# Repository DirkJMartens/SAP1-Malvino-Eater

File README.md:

# SAP1-Malvino-Eater
Wire wrapped implementation of Albert Malvino's SAP1 computer, similar to Ben Eater's "8 bit CPU". 

Like thousands of others, I watched Ben Eater's YouTube series on how to "Build an 8-bit CPU from scratch". 
Ben's video series is based on the "SAP-1 (Simple As Possible 1)" computer, described in "Digital Computer Electronics" 
book by Albert Malvino and Jerald Brown, first released in 1977. 

And like thousands of others, I wanted to build my own. Partly to learn a few things, but above all for fun. 
But I also wanted a few differences: 
  - Use wire-wrapping instead of breadboards. As I could only work on it mostly on weekends and in my spare time,
    I wanted it to be longer-lasting so I could put it away easily and pull it out without first spending time to
    find which wires have been dislodged to get it back working again. 
  - Stay closer to Malvino's original design for the SAP-1. 
  - Add some blinkenlights to visualize:
    - LED bar graphs for W-bus, Accu, B-register, Output-register, Instruction register 
    - LEDs for the control signals (La, Ea, Lb, Eb, Ep, CE ...) and the Program Counter 
    - the ring counter indicating the stage of the Fetch/Execute cycle 
    - the instruction decoder 
  - Added a dual 7-segment display to visualize the W-bus content in HEX-format instead of in binary via LED bar graph.

In short, I wanted it to be much more of a visual CPU that can show which signal gets activated and what it triggers 
in various parts of the CPU. Because I wanted the wiring to be visible, I did not use wire-wrap sockets and wire on the 
bottom of the perfboard. Instead, I soldered pin headers next to each row of IC pins so I had access to each pin on the 
top and wire-wrapped from pinheader pin to pinheader pin. 

Most important specs: 
  - 4 bits address bus with 16 bytes RAM memory and an 8 bits data bus 
  - 4 instructions: Load, Add, Sub and Out
  - Opcodes is the most-significant-nibble (top 4 bits) and memory location is the least (bottom 4 bits) 
  - Clock signal can be single stepped, or auto-run with variable clock speed (up to a few dozen Hz)
  - Done using a mix of various 74-series ICs (LS, F ...) and implemented on a 20cmx30cm (8"x12") perfboard.

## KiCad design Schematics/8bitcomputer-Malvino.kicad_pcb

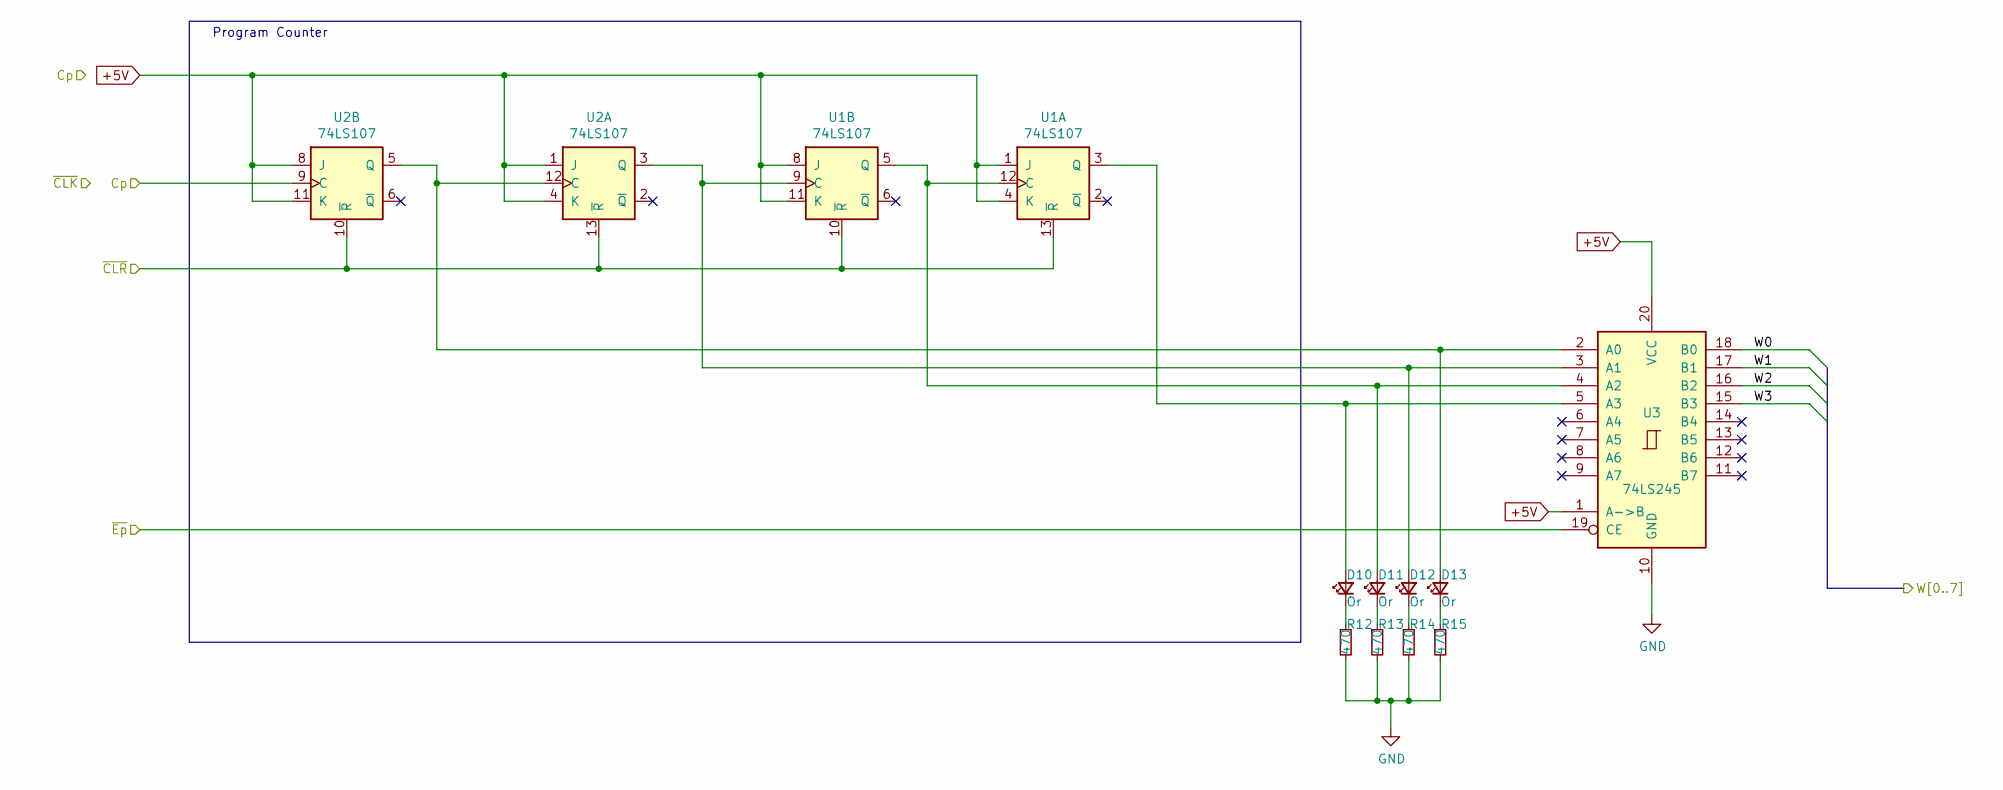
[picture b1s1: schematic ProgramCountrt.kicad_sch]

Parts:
D10, D11, D12, D13: Or; LED_D3.0mm
R12, R13, R14, R15: 470; R_0805_2012Metric
U1, U2: 74LS107; DIP-14_W7.62mm_LongPads
U3: 74LS245; DIP-20_W7.62mm_LongPads

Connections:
+5V: U1.1 (J), U1.4 (K), U1.8 (J), U1.11 (K), U2.1 (J), U2.4 (K), U2.8 (J), U2.11 (K), U3.1 (A->B), U3.20 (VCC); also elsewhere on the board
/1-PowerClock/~CLR: U1.10 (~R), U1.13 (~R), U2.10 (~R), U2.13 (~R); also elsewhere on the board
/2-ProgramCounter/~Ep: U3.19 (CE); also elsewhere on the board
/4-16x8RAM/W0: U3.18 (B0); also elsewhere on the board
/4-16x8RAM/W1: U3.17 (B1); also elsewhere on the board
/4-16x8RAM/W2: U3.16 (B2); also elsewhere on the board
/4-16x8RAM/W3: U3.15 (B3); also elsewhere on the board
/9-InstrControlRing/T2: U2.9 (C); also elsewhere on the board
GND: R12.2, R13.2, R14.2, R15.2, U3.10 (GND); also elsewhere on the board
unnamed: D10.1 (K), R12.1
unnamed: D10.2 (A), U1.3 (Q), U3.5 (A3)
unnamed: D11.1 (K), R13.1
unnamed: D11.2 (A), U1.5 (Q), U1.12 (C), U3.4 (A2)
unnamed: D12.1 (K), R14.1
unnamed: D12.2 (A), U1.9 (C), U2.3 (Q), U3.3 (A1)
unnamed: D13.1 (K), R15.1
unnamed: D13.2 (A), U2.5 (Q), U2.12 (C), U3.2 (A0)

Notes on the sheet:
Program Counter

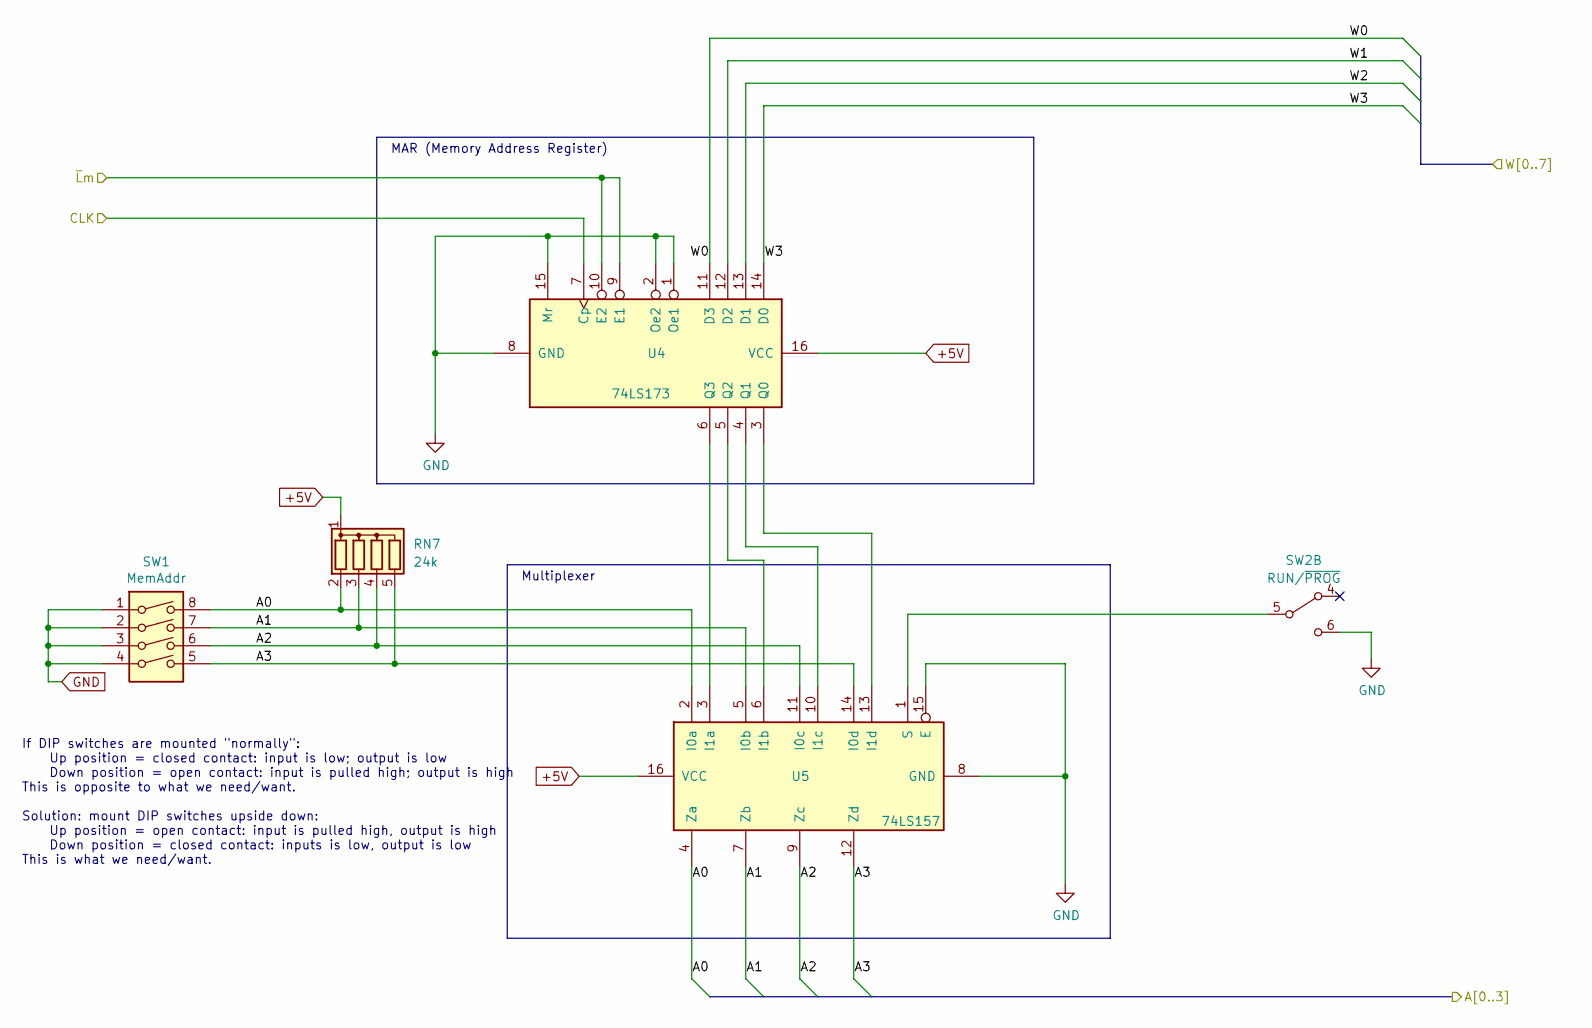
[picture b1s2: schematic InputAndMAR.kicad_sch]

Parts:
RN7: 24k; R_Array_SIP5
SW1: MemAddr; SW_DIP_SPSTx04_Slide_9.78x12.34mm_W7.62mm_P2.54mm
SW2: RUN/~{PROG}; SW_CuK_JS202011AQN_DPDT_Angled
U4: 74LS173; DIP-16_W7.62mm_LongPads
U5: 74LS157; DIP-16_W7.62mm_LongPads

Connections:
+5V: RN7.1 (common), U4.16 (VCC), U5.16 (VCC); also elsewhere on the board
/1-PowerClock/CLK: U4.7 (Cp); also elsewhere on the board
/3-InputAndMAR/A0: RN7.2 (R1), SW1.8, U5.2 (I0a), U5.4 (Za); also elsewhere on the board
/3-InputAndMAR/A1: RN7.3 (R2), SW1.7, U5.5 (I0b), U5.7 (Zb); also elsewhere on the board
/3-InputAndMAR/A2: RN7.4 (R3), SW1.6, U5.9 (Zc), U5.11 (I0c); also elsewhere on the board
/3-InputAndMAR/A3: RN7.5 (R4), SW1.5, U5.12 (Zd), U5.14 (I0d); also elsewhere on the board
/3-InputAndMAR/~Lm: U4.9 (E1), U4.10 (E2); also elsewhere on the board
/4-16x8RAM/W0: U4.11 (D3); also elsewhere on the board
/4-16x8RAM/W1: U4.12 (D2); also elsewhere on the board
/4-16x8RAM/W2: U4.13 (D1); also elsewhere on the board
/4-16x8RAM/W3: U4.14 (D0); also elsewhere on the board
GND: SW1.1, SW1.2, SW1.3, SW1.4, SW2.6 (C), U4.1 (Oe1), U4.2 (Oe2), U4.8 (GND), U4.15 (Mr), U5.8 (GND), U5.15 (E); also elsewhere on the board
unnamed: U4.3 (Q0), U5.13 (I1d)
unnamed: U4.4 (Q1), U5.10 (I1c)
unnamed: U4.5 (Q2), U5.6 (I1b)
unnamed: U4.6 (Q3), U5.3 (I1a)
unnamed: SW2.5 (B), U5.1 (S)

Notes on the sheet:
Multiplexer
If DIP switches are mounted "normally": Up position = closed contact: input is low; output is low Down position = open contact: input is pulled high; output is high This is opposite to what we need/want. Solution: mount DIP switches upside down: Up position = open contact: input is pulled high, out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
MAR (Memory Address Register)

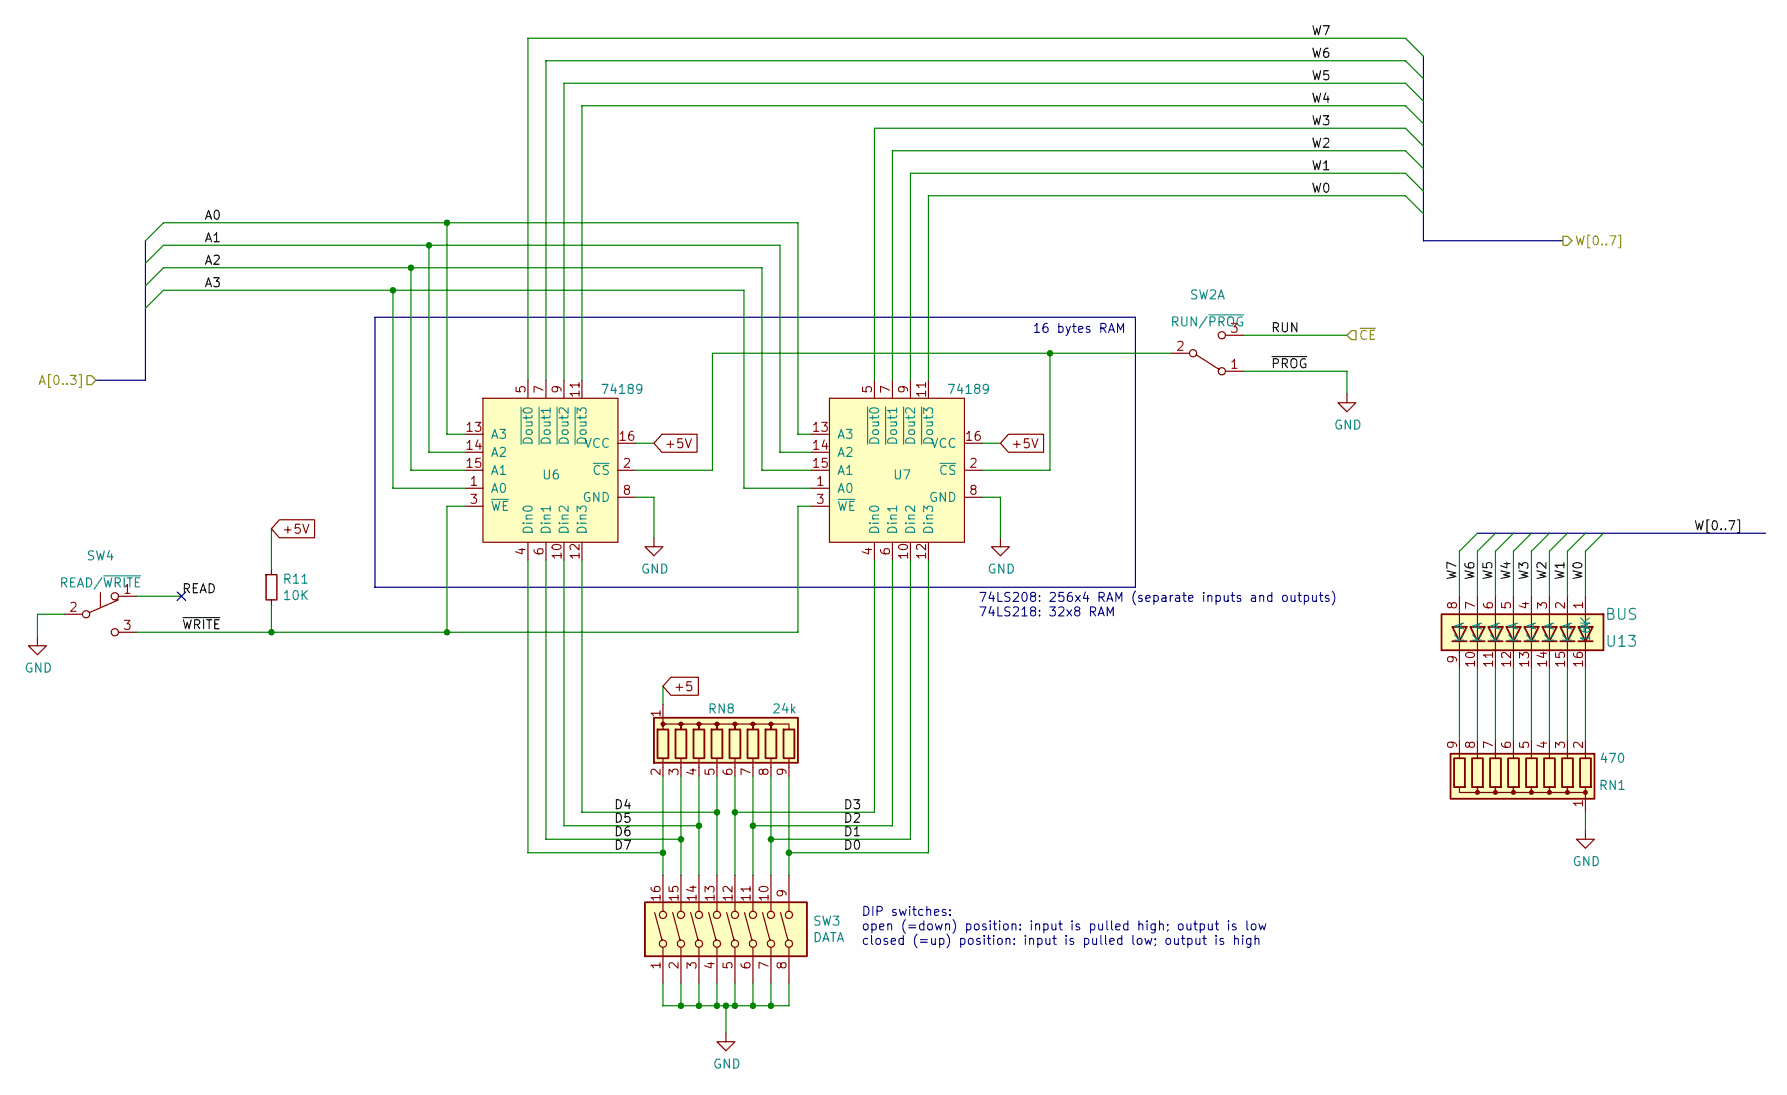
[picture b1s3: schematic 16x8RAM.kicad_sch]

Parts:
R11: 10K; R_Axial_DIN0207_L6.3mm_D2.5mm_P7.62mm_Horizontal
RN1: 470; R_Array_SIP9
RN8: 24k; R_Array_SIP9
SW2: RUN/~{PROG}; SW_CuK_JS202011AQN_DPDT_Angled
SW3: DATA; SW_DIP_SPSTx08_Slide_6.7x21.88mm_W7.62mm_P2.54mm_LowProfile
SW4: READ/~{WRITE}; SW_Push_1P2T_Vertical_E-Switch_800UDP8P1A1M6
U6, U7: 74189; DIP-16_W7.62mm_LongPads
U13: BUS; DIP-16_W7.62mm_LongPads

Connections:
+5: RN8.1 (common); also elsewhere on the board
+5V: R11.1, U6.16 (VCC), U7.16 (VCC); also elsewhere on the board
/3-InputAndMAR/A0: U6.13 (A3), U7.13 (A3); also elsewhere on the board
/3-InputAndMAR/A1: U6.14 (A2), U7.14 (A2); also elsewhere on the board
/3-InputAndMAR/A2: U6.15 (A1), U7.15 (A1); also elsewhere on the board
/3-InputAndMAR/A3: U6.1 (A0), U7.1 (A0); also elsewhere on the board
/4-16x8RAM/D0: RN8.9 (R8), SW3.9, U7.12 (Din3)
/4-16x8RAM/D1: RN8.8 (R7), SW3.10, U7.10 (Din2)
/4-16x8RAM/D2: RN8.7 (R6), SW3.11, U7.6 (Din1)
/4-16x8RAM/D3: RN8.6 (R5), SW3.12, U7.4 (Din0)
/4-16x8RAM/D4: RN8.5 (R4), SW3.13, U6.12 (Din3)
/4-16x8RAM/D5: RN8.4 (R3), SW3.14, U6.10 (Din2)
/4-16x8RAM/D6: RN8.3 (R2), SW3.15, U6.6 (Din1)
/4-16x8RAM/D7: RN8.2 (R1), SW3.16, U6.4 (Din0)
/4-16x8RAM/READ: SW4.1 (A)
/4-16x8RAM/RUN: SW2.3 (C); also elsewhere on the board
/4-16x8RAM/W0: U7.11 (~Dout3), U13.1 (A); also elsewhere on the board
/4-16x8RAM/W1: U7.9 (~Dout2), U13.2 (A); also elsewhere on the board
/4-16x8RAM/W2: U7.7 (~Dout1), U13.3 (A); also elsewhere on the board
/4-16x8RAM/W3: U7.5 (~Dout0), U13.4 (A); also elsewhere on the board
/4-16x8RAM/W4: U6.11 (~Dout3), U13.5 (A); also elsewhere on the board
/4-16x8RAM/W5: U6.9 (~Dout2), U13.6 (A); also elsewhere on the board
/4-16x8RAM/W6: U6.7 (~Dout1), U13.7 (A); also elsewhere on the board
/4-16x8RAM/W7: U6.5 (~Dout0), U13.8 (A); also elsewhere on the board
/4-16x8RAM/~WRITE: R11.2, SW4.3 (C), U6.3 (~WE), U7.3 (~WE)
GND: RN1.1 (common), SW2.1 (A), SW3.1, SW3.2, SW3.3, SW3.4, SW3.5, SW3.6, SW3.7, SW3.8, SW4.2 (B), U6.8 (GND), U7.8 (GND); also elsewhere on the board
unnamed: RN1.2 (R1), U13.16 (16K)
unnamed: RN1.3 (R2), U13.15 (K)
unnamed: RN1.4 (R3), U13.14 (K)
unnamed: RN1.5 (R4), U13.13 (K)
unnamed: RN1.6 (R5), U13.12 (K)
unnamed: RN1.7 (R6), U13.11 (K)
unnamed: RN1.8 (R7), U13.10 (K)
unnamed: RN1.9 (R8), U13.9 (K)
unnamed: SW2.2 (B), U6.2 (~CS), U7.2 (~CS)

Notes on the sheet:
DIP switches: open (=down) position: input is pulled high; output is low closed (=up) position: input is pulled low; output is high
16 bytes RAM
74LS208: 256x4 RAM (separate inputs and outputs) 74LS218: 32x8 RAM

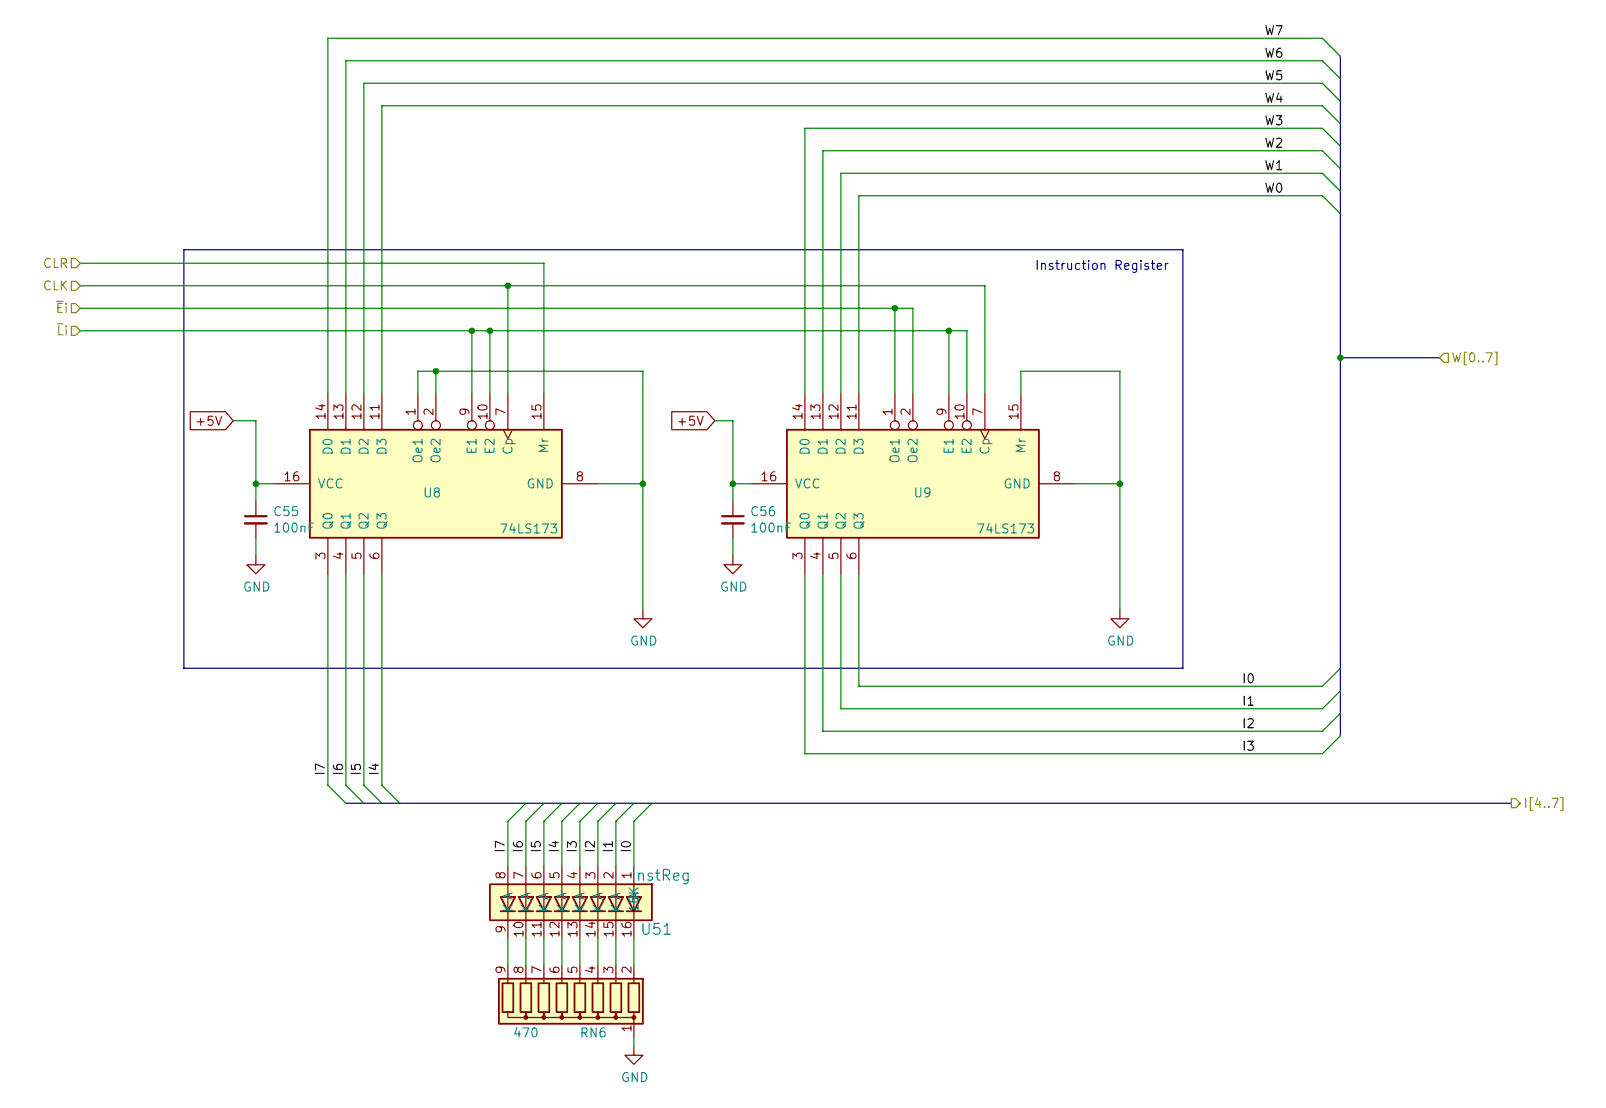
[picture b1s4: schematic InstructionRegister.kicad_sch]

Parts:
C55, C56: 100nF; C_0805_2012Metric
RN6: 470; R_Array_SIP9
U8, U9: 74LS173; DIP-16_W7.62mm_LongPads
U51: InstReg; DIP-16_W7.62mm_LongPads

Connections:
+5V: C55.1, C56.1, U8.16 (VCC), U9.16 (VCC); also elsewhere on the board
/1-PowerClock/CLK: U8.7 (Cp), U9.7 (Cp); also elsewhere on the board
/1-PowerClock/CLR: U8.15 (Mr); also elsewhere on the board
/4-16x8RAM/W0: U9.11 (D3); also elsewhere on the board
/4-16x8RAM/W1: U9.12 (D2); also elsewhere on the board
/4-16x8RAM/W2: U9.13 (D1); also elsewhere on the board
/4-16x8RAM/W3: U9.14 (D0); also elsewhere on the board
/4-16x8RAM/W4: U8.11 (D3); also elsewhere on the board
/4-16x8RAM/W5: U8.12 (D2); also elsewhere on the board
/4-16x8RAM/W6: U8.13 (D1); also elsewhere on the board
/4-16x8RAM/W7: U8.14 (D0); also elsewhere on the board
/5-InstructionRegister/I0: U9.6 (Q3), U51.1 (A)
/5-InstructionRegister/I1: U9.5 (Q2), U51.2 (A)
/5-InstructionRegister/I2: U9.4 (Q1), U51.3 (A)
/5-InstructionRegister/I3: U9.3 (Q0), U51.4 (A)
/5-InstructionRegister/I4: U8.6 (Q3), U51.5 (A); also elsewhere on the board
/5-InstructionRegister/I5: U8.5 (Q2), U51.6 (A); also elsewhere on the board
/5-InstructionRegister/I6: U8.4 (Q1), U51.7 (A); also elsewhere on the board
/5-InstructionRegister/I7: U8.3 (Q0), U51.8 (A); also elsewhere on the board
/5-InstructionRegister/~Ei: U9.1 (Oe1), U9.2 (Oe2); also elsewhere on the board
/5-InstructionRegister/~Li: U8.9 (E1), U8.10 (E2), U9.9 (E1), U9.10 (E2); also elsewhere on the board
GND: C55.2, C56.2, RN6.1 (common), U8.1 (Oe1), U8.2 (Oe2), U8.8 (GND), U9.8 (GND), U9.15 (Mr); also elsewhere on the board
unnamed: RN6.2 (R1), U51.16 (16K)
unnamed: RN6.3 (R2), U51.15 (K)
unnamed: RN6.4 (R3), U51.14 (K)
unnamed: RN6.5 (R4), U51.13 (K)
unnamed: RN6.6 (R5), U51.12 (K)
unnamed: RN6.7 (R6), U51.11 (K)
unnamed: RN6.8 (R7), U51.10 (K)
unnamed: RN6.9 (R8), U51.9 (K)

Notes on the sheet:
Instruction Register

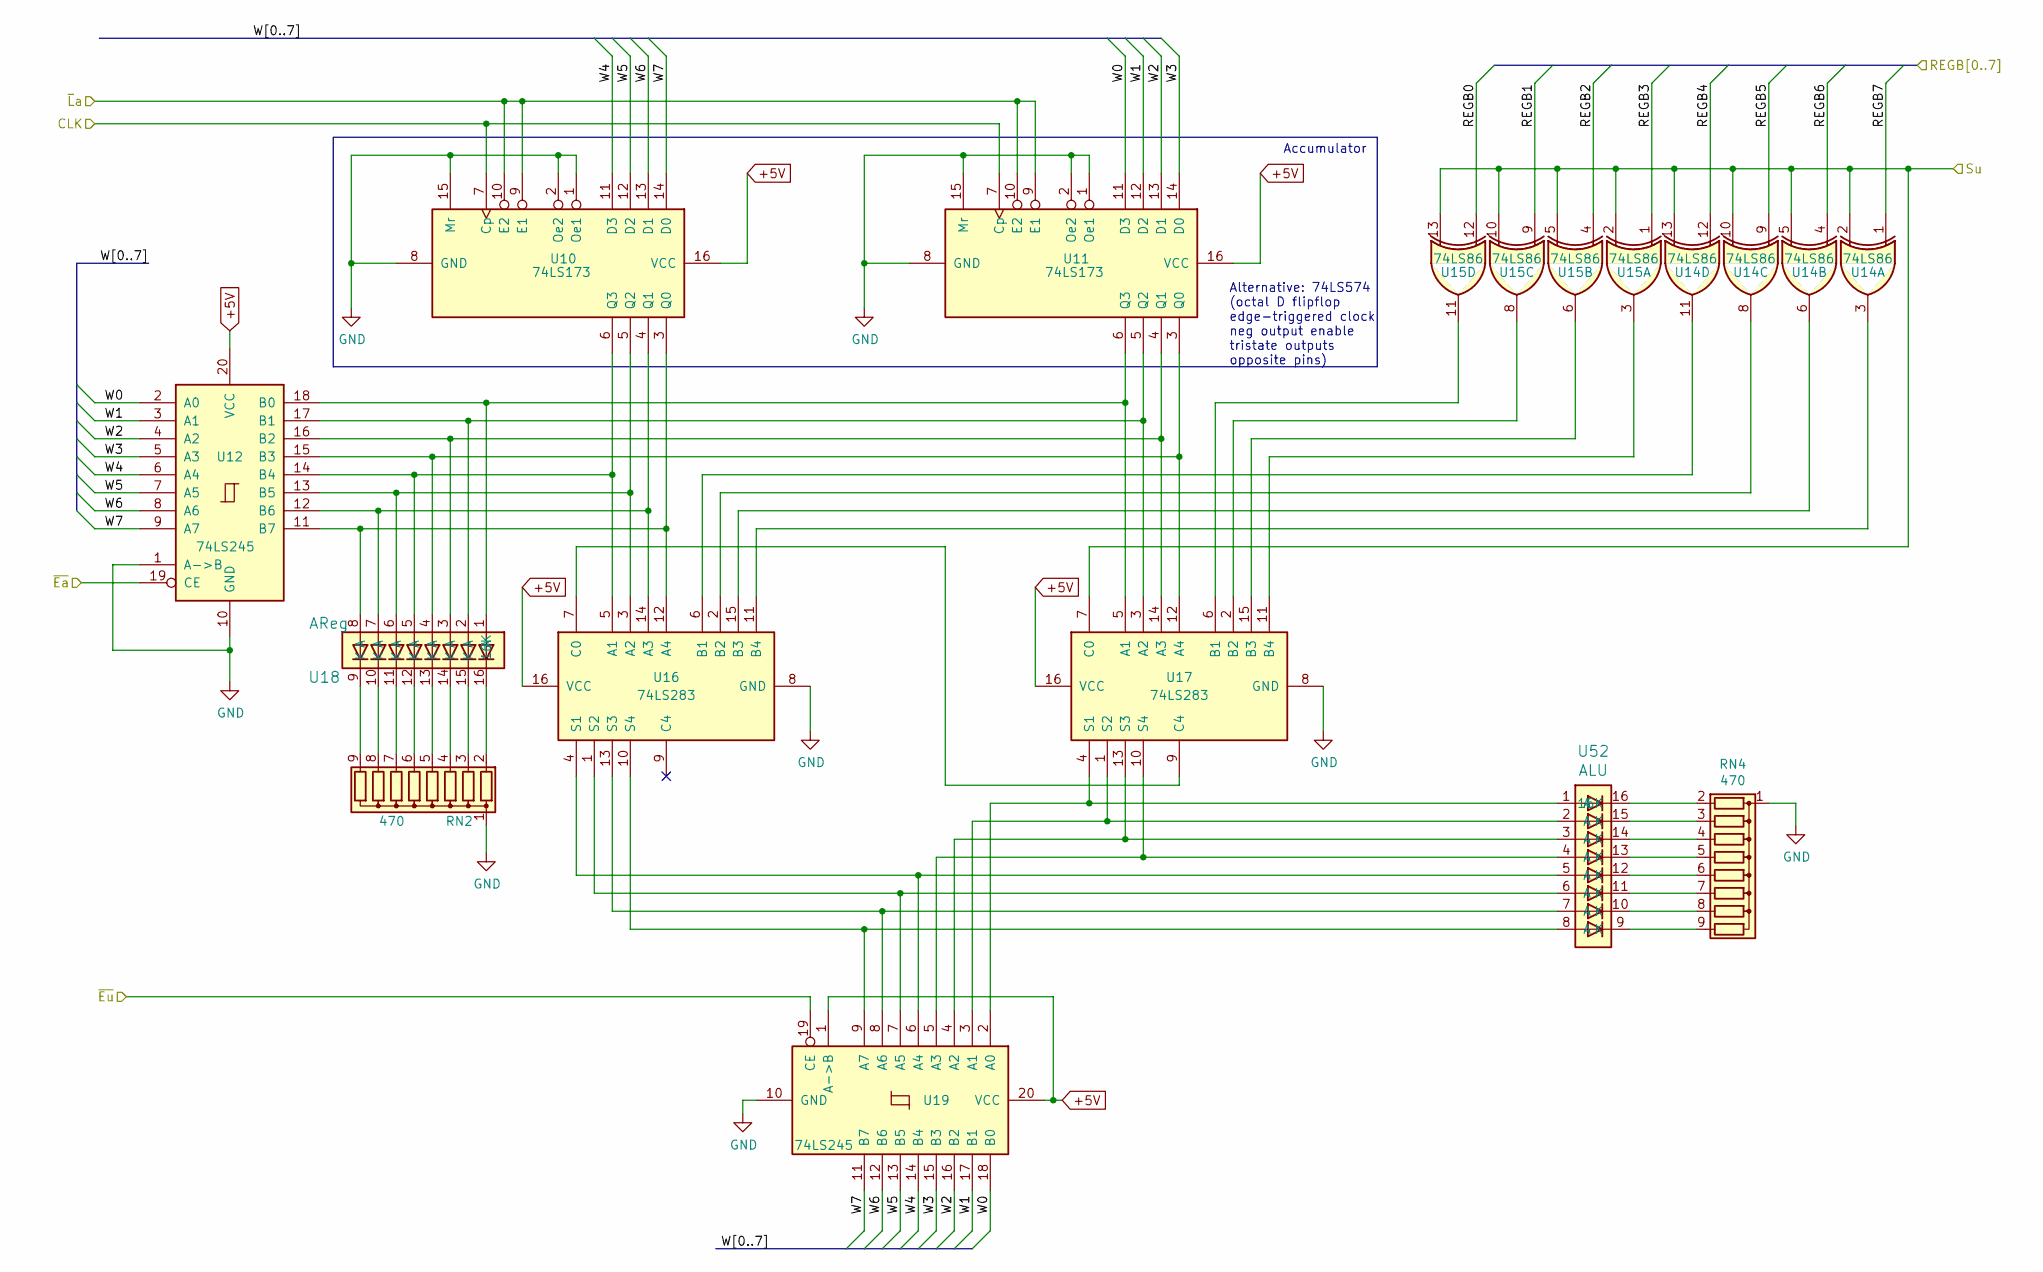
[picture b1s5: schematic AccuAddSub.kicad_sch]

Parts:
RN2, RN4: 470; R_Array_SIP9
U10, U11: 74LS173; DIP-16_W7.62mm_LongPads
U12, U19: 74LS245; DIP-20_W7.62mm_LongPads
U14, U15: 74LS86; DIP-14_W7.62mm_LongPads
U16, U17: 74LS283; DIP-16_W7.62mm_LongPads
U18: AReg; DIP-16_W7.62mm_LongPads
U52: ALU; DIP-16_W7.62mm_LongPads

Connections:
+5V: U10.16 (VCC), U11.16 (VCC), U12.20 (VCC), U16.16 (VCC), U17.16 (VCC), U19.1 (A->B), U19.20 (VCC); also elsewhere on the board
/1-PowerClock/CLK: U10.7 (Cp), U11.7 (Cp); also elsewhere on the board
/6-AccuAddSub/REGB0: U15.12; also elsewhere on the board
/6-AccuAddSub/REGB1: U15.9; also elsewhere on the board
/6-AccuAddSub/REGB2: U15.4; also elsewhere on the board
/6-AccuAddSub/REGB3: U15.1; also elsewhere on the board
/6-AccuAddSub/REGB4: U14.12; also elsewhere on the board
/6-AccuAddSub/REGB5: U14.9; also elsewhere on the board
/6-AccuAddSub/REGB6: U14.4; also elsewhere on the board
/6-AccuAddSub/REGB7: U14.1; also elsewhere on the board
/6-AccuAddSub/Su: U14.2, U14.5, U14.10, U14.13, U15.2, U15.5, U15.10, U15.13, U17.7 (C0); also elsewhere on the board
/6-AccuAddSub/W0: U11.11 (D3), U12.2 (A0), U19.18 (B0)
/6-AccuAddSub/W1: U11.12 (D2), U12.3 (A1), U19.17 (B1)
/6-AccuAddSub/W2: U11.13 (D1), U12.4 (A2), U19.16 (B2)
/6-AccuAddSub/W3: U11.14 (D0), U12.5 (A3), U19.15 (B3)
/6-AccuAddSub/W4: U10.11 (D3), U12.6 (A4), U19.14 (B4)
/6-AccuAddSub/W5: U10.12 (D2), U12.7 (A5), U19.13 (B5)
/6-AccuAddSub/W6: U10.13 (D1), U12.8 (A6), U19.12 (B6)
/6-AccuAddSub/W7: U10.14 (D0), U12.9 (A7), U19.11 (B7)
/6-AccuAddSub/~Ea: U12.19 (CE); also elsewhere on the board
/6-AccuAddSub/~Eu: U19.19 (CE); also elsewhere on the board
/6-AccuAddSub/~La: U10.9 (E1), U10.10 (E2), U11.9 (E1), U11.10 (E2); also elsewhere on the board
GND: RN2.1 (common), RN4.1 (common), U10.1 (Oe1), U10.2 (Oe2), U10.8 (GND), U10.15 (Mr), U11.1 (Oe1), U11.2 (Oe2), U11.8 (GND), U11.15 (Mr), U12.1 (A->B), U12.10 (GND), U16.8 (GND), U17.8 (GND), U19.10 (GND); also elsewhere on the board
unnamed: RN2.2 (R1), U18.16 (16K)
unnamed: RN2.3 (R2), U18.15 (K)
unnamed: RN2.4 (R3), U18.14 (K)
unnamed: RN2.5 (R4), U18.13 (K)
unnamed: RN2.6 (R5), U18.12 (K)
unnamed: RN2.7 (R6), U18.11 (K)
unnamed: RN2.8 (R7), U18.10 (K)
unnamed: RN2.9 (R8), U18.9 (K)
unnamed: RN4.2 (R1), U52.16 (16K)
unnamed: RN4.3 (R2), U52.15 (K)
unnamed: RN4.4 (R3), U52.14 (K)
unnamed: RN4.5 (R4), U52.13 (K)
unnamed: RN4.6 (R5), U52.12 (K)
unnamed: RN4.7 (R6), U52.11 (K)
unnamed: RN4.8 (R7), U52.10 (K)
unnamed: RN4.9 (R8), U52.9 (K)
unnamed: U10.3 (Q0), U12.11 (B7), U16.12 (A4), U18.8 (A)
unnamed: U10.4 (Q1), U12.12 (B6), U16.14 (A3), U18.7 (A)
unnamed: U10.5 (Q2), U12.13 (B5), U16.3 (A2), U18.6 (A)
unnamed: U10.6 (Q3), U12.14 (B4), U16.5 (A1), U18.5 (A)
unnamed: U11.3 (Q0), U12.15 (B3), U17.12 (A4), U18.4 (A)
unnamed: U11.4 (Q1), U12.16 (B2), U17.14 (A3), U18.3 (A)
unnamed: U11.5 (Q2), U12.17 (B1), U17.3 (A2), U18.2 (A)
unnamed: U11.6 (Q3), U12.18 (B0), U17.5 (A1), U18.1 (A)
unnamed: U14.3, U16.11 (B4)
unnamed: U14.6, U16.15 (B3)
unnamed: U14.8, U16.2 (B2)
unnamed: U14.11, U16.6 (B1)
unnamed: U15.3, U17.11 (B4)
unnamed: U15.6, U17.15 (B3)
unnamed: U15.8, U17.2 (B2)
unnamed: U15.11, U17.6 (B1)
unnamed: U16.1 (S2), U19.7 (A5), U52.6 (A)
unnamed: U16.4 (S1), U19.6 (A4), U52.5 (A)
unnamed: U16.7 (C0), U17.9 (C4)
unnamed: U16.10 (S4), U19.9 (A7), U52.8 (A)
unnamed: U16.13 (S3), U19.8 (A6), U52.7 (A)
unnamed: U17.1 (S2), U19.3 (A1), U52.2 (A)
unnamed: U17.4 (S1), U19.2 (A0), U52.1 (A)
unnamed: U17.10 (S4), U19.5 (A3), U52.4 (A)
unnamed: U17.13 (S3), U19.4 (A2), U52.3 (A)

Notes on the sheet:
Accumulator
Alternative: 74LS574 (octal D flipflop edge-triggered clock neg output enable tristate outputs opposite pins)

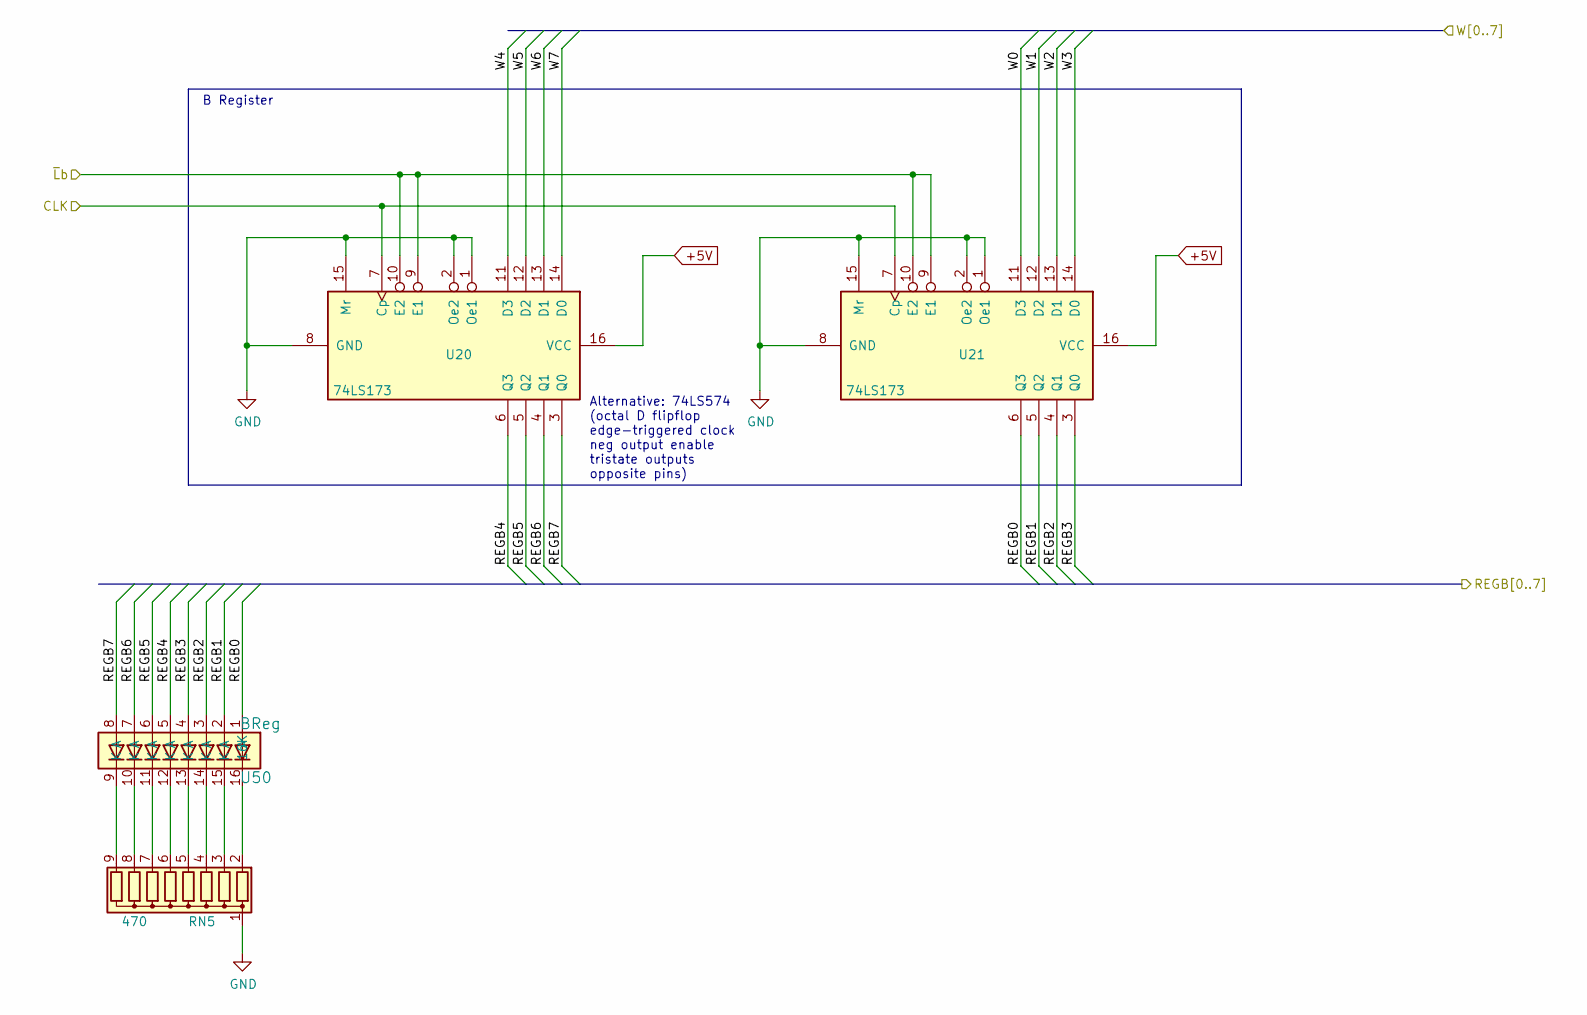
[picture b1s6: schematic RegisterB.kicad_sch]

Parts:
RN5: 470; R_Array_SIP9
U20, U21: 74LS173; DIP-16_W7.62mm_LongPads
U50: BReg; DIP-16_W7.62mm_LongPads

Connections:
+5V: U20.16 (VCC), U21.16 (VCC); also elsewhere on the board
/1-PowerClock/CLK: U20.7 (Cp), U21.7 (Cp); also elsewhere on the board
/4-16x8RAM/W0: U21.11 (D3); also elsewhere on the board
/4-16x8RAM/W1: U21.12 (D2); also elsewhere on the board
/4-16x8RAM/W2: U21.13 (D1); also elsewhere on the board
/4-16x8RAM/W3: U21.14 (D0); also elsewhere on the board
/4-16x8RAM/W4: U20.11 (D3); also elsewhere on the board
/4-16x8RAM/W5: U20.12 (D2); also elsewhere on the board
/4-16x8RAM/W6: U20.13 (D1); also elsewhere on the board
/4-16x8RAM/W7: U20.14 (D0); also elsewhere on the board
/6-AccuAddSub/REGB0: U21.6 (Q3), U50.1 (A); also elsewhere on the board
/6-AccuAddSub/REGB1: U21.5 (Q2), U50.2 (A); also elsewhere on the board
/6-AccuAddSub/REGB2: U21.4 (Q1), U50.3 (A); also elsewhere on the board
/6-AccuAddSub/REGB3: U21.3 (Q0), U50.4 (A); also elsewhere on the board
/6-AccuAddSub/REGB4: U20.6 (Q3), U50.5 (A); also elsewhere on the board
/6-AccuAddSub/REGB5: U20.5 (Q2), U50.6 (A); also elsewhere on the board
/6-AccuAddSub/REGB6: U20.4 (Q1), U50.7 (A); also elsewhere on the board
/6-AccuAddSub/REGB7: U20.3 (Q0), U50.8 (A); also elsewhere on the board
/7-RegisterB/~Lb: U20.9 (E1), U20.10 (E2), U21.9 (E1), U21.10 (E2); also elsewhere on the board
GND: RN5.1 (common), U20.1 (Oe1), U20.2 (Oe2), U20.8 (GND), U20.15 (Mr), U21.1 (Oe1), U21.2 (Oe2), U21.8 (GND), U21.15 (Mr); also elsewhere on the board
unnamed: RN5.2 (R1), U50.16 (16K)
unnamed: RN5.3 (R2), U50.15 (K)
unnamed: RN5.4 (R3), U50.14 (K)
unnamed: RN5.5 (R4), U50.13 (K)
unnamed: RN5.6 (R5), U50.12 (K)
unnamed: RN5.7 (R6), U50.11 (K)
unnamed: RN5.8 (R7), U50.10 (K)
unnamed: RN5.9 (R8), U50.9 (K)

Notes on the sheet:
Alternative: 74LS574 (octal D flipflop edge-triggered clock neg output enable tristate outputs opposite pins)
B Register

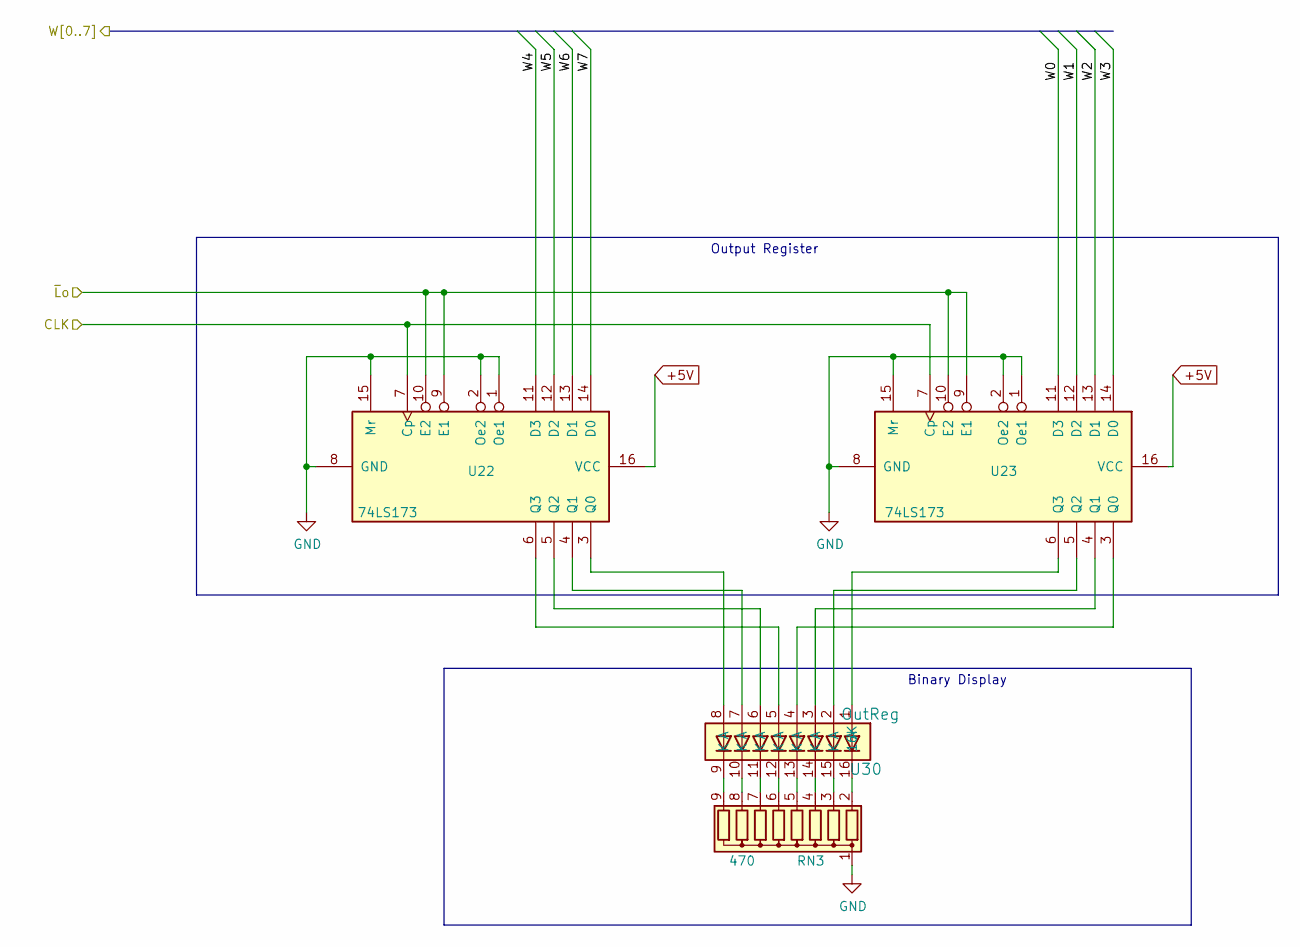
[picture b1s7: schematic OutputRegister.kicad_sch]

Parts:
RN3: 470; R_Array_SIP9
U22, U23: 74LS173; DIP-16_W7.62mm_LongPads
U30: OutReg; DIP-16_W7.62mm_LongPads

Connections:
+5V: U22.16 (VCC), U23.16 (VCC); also elsewhere on the board
/1-PowerClock/CLK: U22.7 (Cp), U23.7 (Cp); also elsewhere on the board
/4-16x8RAM/W0: U23.11 (D3); also elsewhere on the board
/4-16x8RAM/W1: U23.12 (D2); also elsewhere on the board
/4-16x8RAM/W2: U23.13 (D1); also elsewhere on the board
/4-16x8RAM/W3: U23.14 (D0); also elsewhere on the board
/4-16x8RAM/W4: U22.11 (D3); also elsewhere on the board
/4-16x8RAM/W5: U22.12 (D2); also elsewhere on the board
/4-16x8RAM/W6: U22.13 (D1); also elsewhere on the board
/4-16x8RAM/W7: U22.14 (D0); also elsewhere on the board
/8-OutputRegister/~Lo: U22.9 (E1), U22.10 (E2), U23.9 (E1), U23.10 (E2); also elsewhere on the board
GND: RN3.1 (common), U22.1 (Oe1), U22.2 (Oe2), U22.8 (GND), U22.15 (Mr), U23.1 (Oe1), U23.2 (Oe2), U23.8 (GND), U23.15 (Mr); also elsewhere on the board
unnamed: RN3.2 (R1), U30.16 (16K)
unnamed: RN3.3 (R2), U30.15 (K)
unnamed: RN3.4 (R3), U30.14 (K)
unnamed: RN3.5 (R4), U30.13 (K)
unnamed: RN3.6 (R5), U30.12 (K)
unnamed: RN3.7 (R6), U30.11 (K)
unnamed: RN3.8 (R7), U30.10 (K)
unnamed: RN3.9 (R8), U30.9 (K)
unnamed: U22.3 (Q0), U30.8 (A)
unnamed: U22.4 (Q1), U30.7 (A)
unnamed: U22.5 (Q2), U30.6 (A)
unnamed: U22.6 (Q3), U30.5 (A)
unnamed: U23.3 (Q0), U30.4 (A)
unnamed: U23.4 (Q1), U30.3 (A)
unnamed: U23.5 (Q2), U30.2 (A)
unnamed: U23.6 (Q3), U30.1 (A)

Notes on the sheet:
Binary Display
Output Register
